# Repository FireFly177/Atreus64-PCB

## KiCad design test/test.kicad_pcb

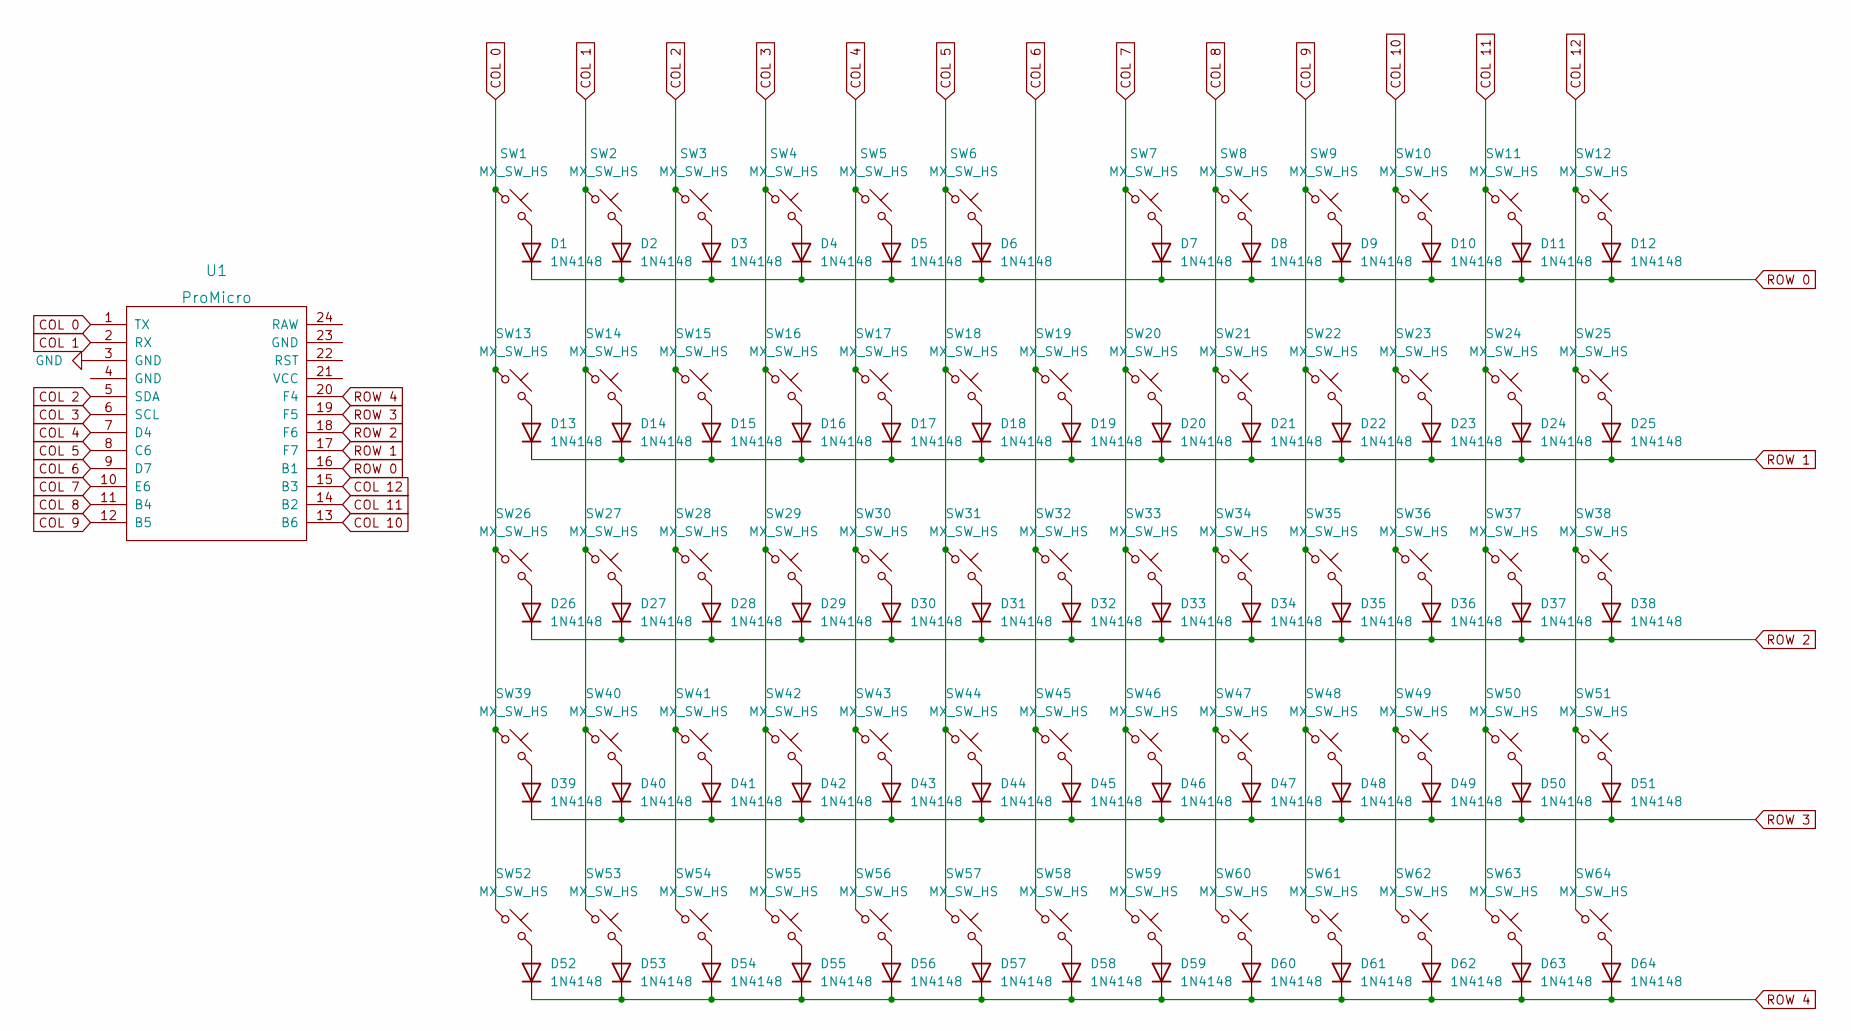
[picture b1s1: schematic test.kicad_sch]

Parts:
D1, D2, D3, D4, D5, D6, D7, D8, D9, D10, D11, D12, D13, D14, D15, D16, D17, D18, D19, D20, D21, D22, D23, D24, D25, D26, D27, D28, D29, D30, D31, D32, D33, D34, D35, D36, D37, D38, D39, D40, D41, D42, D43, D44, D45, D46, D47, D48, D49, D50, D51, D52, D53, D54, D55, D56, D57, D58, D59, D60, D61, D62, D63, D64: 1N4148; D_DO-35_SOD27_P7.62mm_Horizontal
SW1, SW2, SW3, SW4, SW5, SW6, SW7, SW8, SW9, SW10, SW11, SW12, SW13, SW14, SW15, SW16, SW17, SW18, SW19, SW20, SW21, SW22, SW23, SW24, SW25, SW26, SW27, SW28, SW29, SW30, SW31, SW32, SW33, SW34, SW35, SW36, SW37, SW38, SW39, SW40, SW41, SW42, SW43, SW44, SW45, SW46, SW47, SW48, SW49, SW50, SW51, SW52, SW53, SW54, SW55, SW56, SW57, SW58, SW59, SW60, SW61, SW62, SW63, SW64: MX_SW_HS; MXOnly-1U-Hotswap
U1: ProMicro

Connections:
COL 0: SW1.1, SW13.1, SW26.1, SW39.1, SW52.1, U1.1 (TX)
COL 1: SW2.1, SW14.1, SW27.1, SW40.1, SW53.1, U1.2 (RX)
COL 2: SW3.1, SW15.1, SW28.1, SW41.1, SW54.1, U1.5 (SDA)
COL 3: SW4.1, SW16.1, SW29.1, SW42.1, SW55.1, U1.6 (SCL)
COL 4: SW5.1, SW17.1, SW30.1, SW43.1, SW56.1, U1.7 (D4)
COL 5: SW6.1, SW18.1, SW31.1, SW44.1, SW57.1, U1.8 (C6)
COL 6: SW19.1, SW32.1, SW45.1, SW58.1, U1.9 (D7)
COL 7: SW7.1, SW20.1, SW33.1, SW46.1, SW59.1, U1.10 (E6)
COL 8: SW8.1, SW21.1, SW34.1, SW47.1, SW60.1, U1.11 (B4)
COL 9: SW9.1, SW22.1, SW35.1, SW48.1, SW61.1, U1.12 (B5)
COL 10: SW10.1, SW23.1, SW36.1, SW49.1, SW62.1, U1.13 (B6)
COL 11: SW11.1, SW24.1, SW37.1, SW50.1, SW63.1, U1.14 (B2)
COL 12: SW12.1, SW25.1, SW38.1, SW51.1, SW64.1, U1.15 (B3)
GND: U1.3 (GND)
unnamed: D1.2 (A), SW1.2
unnamed: D2.2 (A), SW2.2
unnamed: D3.2 (A), SW3.2
unnamed: D4.2 (A), SW4.2
unnamed: D5.2 (A), SW5.2
unnamed: D6.2 (A), SW6.2
unnamed: D7.2 (A), SW7.2
unnamed: D8.2 (A), SW8.2
unnamed: D9.2 (A), SW9.2
unnamed: D10.2 (A), SW10.2
unnamed: D11.2 (A), SW11.2
unnamed: D12.2 (A), SW12.2
unnamed: D13.2 (A), SW13.2
unnamed: D14.2 (A), SW14.2
unnamed: D15.2 (A), SW15.2
unnamed: D16.2 (A), SW16.2
unnamed: D17.2 (A), SW17.2
unnamed: D18.2 (A), SW18.2
unnamed: D19.2 (A), SW19.2
unnamed: D20.2 (A), SW20.2
unnamed: D21.2 (A), SW21.2
unnamed: D22.2 (A), SW22.2
unnamed: D23.2 (A), SW23.2
unnamed: D24.2 (A), SW24.2
unnamed: D25.2 (A), SW25.2
unnamed: D26.2 (A), SW26.2
unnamed: D27.2 (A), SW27.2
unnamed: D28.2 (A), SW28.2
unnamed: D29.2 (A), SW29.2
unnamed: D30.2 (A), SW30.2
unnamed: D31.2 (A), SW31.2
unnamed: D32.2 (A), SW32.2
unnamed: D33.2 (A), SW33.2
unnamed: D34.2 (A), SW34.2
unnamed: D35.2 (A), SW35.2
unnamed: D36.2 (A), SW36.2
unnamed: D37.2 (A), SW37.2
unnamed: D38.2 (A), SW38.2
unnamed: D39.2 (A), SW39.2
unnamed: D40.2 (A), SW40.2
unnamed: D41.2 (A), SW41.2
unnamed: D42.2 (A), SW42.2
unnamed: D43.2 (A), SW43.2
unnamed: D44.2 (A), SW44.2
unnamed: D45.2 (A), SW45.2
unnamed: D46.2 (A), SW46.2
unnamed: D47.2 (A), SW47.2
unnamed: D48.2 (A), SW48.2
unnamed: D49.2 (A), SW49.2
unnamed: D50.2 (A), SW50.2
unnamed: D51.2 (A), SW51.2
unnamed: D52.2 (A), SW52.2
unnamed: D53.2 (A), SW53.2
unnamed: D54.2 (A), SW54.2
unnamed: D55.2 (A), SW55.2
unnamed: D56.2 (A), SW56.2
unnamed: D57.2 (A), SW57.2
unnamed: D58.2 (A), SW58.2
unnamed: D59.2 (A), SW59.2
unnamed: D60.2 (A), SW60.2
unnamed: D61.2 (A), SW61.2
unnamed: D62.2 (A), SW62.2
unnamed: D63.2 (A), SW63.2
unnamed: D64.2 (A), SW64.2
ROW 0: D1.1 (K), D2.1 (K), D3.1 (K), D4.1 (K), D5.1 (K), D6.1 (K), D7.1 (K), D8.1 (K), D9.1 (K), D10.1 (K), D11.1 (K), D12.1 (K), U1.16 (B1)
ROW 1: D13.1 (K), D14.1 (K), D15.1 (K), D16.1 (K), D17.1 (K), D18.1 (K), D19.1 (K), D20.1 (K), D21.1 (K), D22.1 (K), D23.1 (K), D24.1 (K), D25.1 (K), U1.17 (F7)
ROW 2: D26.1 (K), D27.1 (K), D28.1 (K), D29.1 (K), D30.1 (K), D31.1 (K), D32.1 (K), D33.1 (K), D34.1 (K), D35.1 (K), D36.1 (K), D37.1 (K), D38.1 (K), U1.18 (F6)
ROW 3: D39.1 (K), D40.1 (K), D41.1 (K), D42.1 (K), D43.1 (K), D44.1 (K), D45.1 (K), D46.1 (K), D47.1 (K), D48.1 (K), D49.1 (K), D50.1 (K), D51.1 (K), U1.19 (F5)
ROW 4: D52.1 (K), D53.1 (K), D54.1 (K), D55.1 (K), D56.1 (K), D57.1 (K), D58.1 (K), D59.1 (K), D60.1 (K), D61.1 (K), D62.1 (K), D63.1 (K), D64.1 (K), U1.20 (F4)

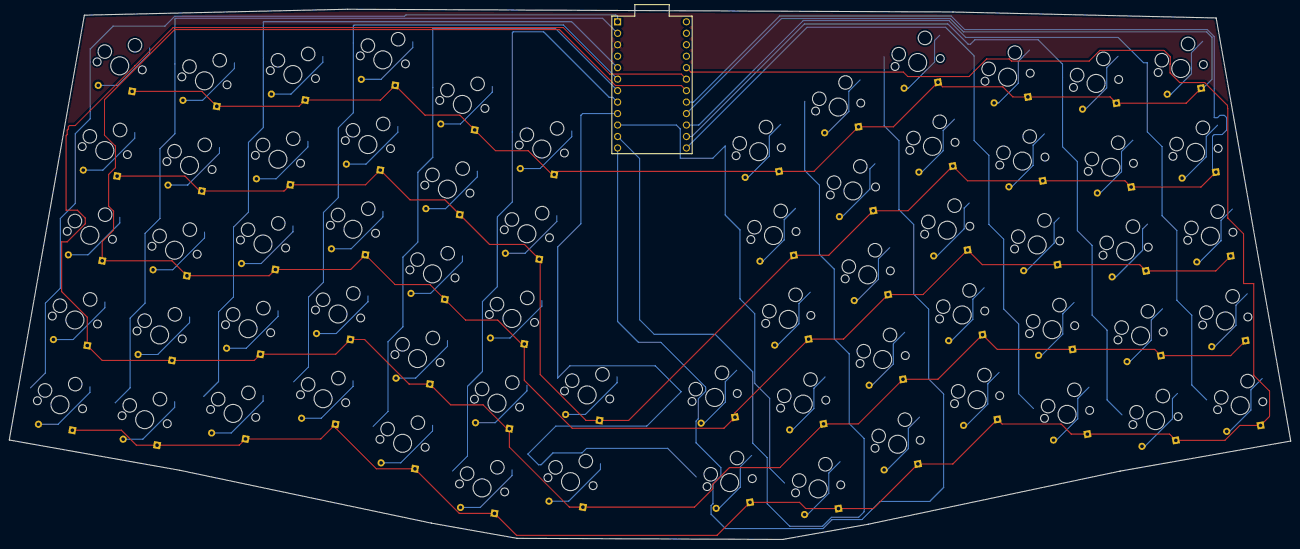
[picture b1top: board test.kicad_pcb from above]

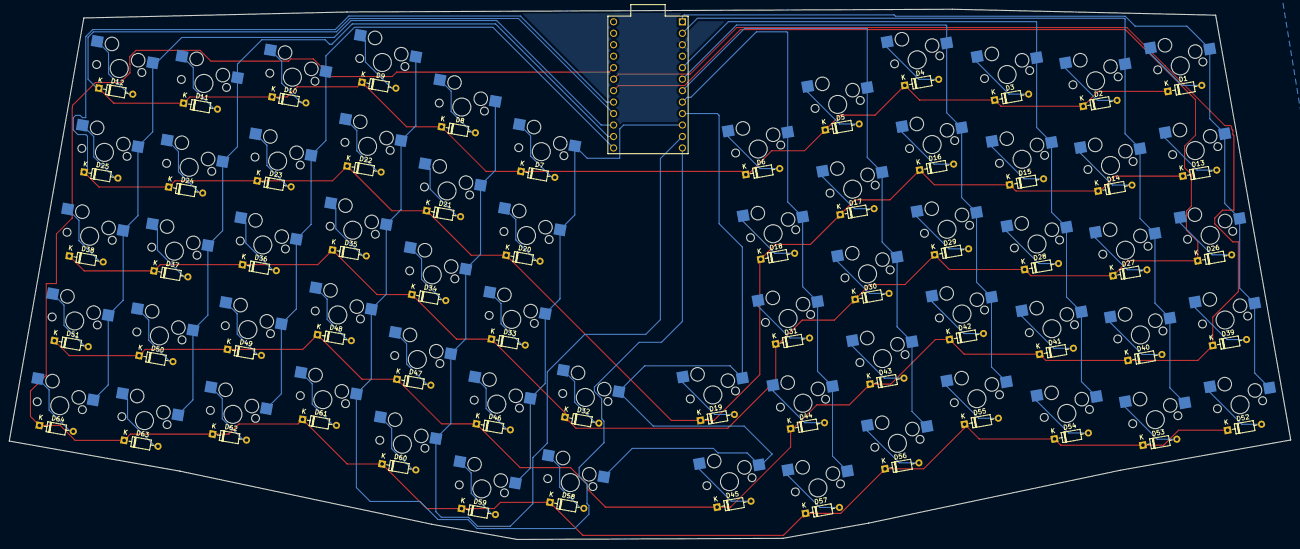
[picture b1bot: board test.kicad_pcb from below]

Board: 2 copper layers, 283.8 x 117.4 mm, 129 parts (64 on the bottom side), 82 nets.

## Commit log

2023-02-20 add traces
